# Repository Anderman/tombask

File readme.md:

Tosot (Gree) Hombask 200Liter

The signal is custom rs485

All message send
```
12-07 12:47:05 frame=7e 7e 00 f0 00 04 90 31 01 64 47 00 (poll slave 0x00)
12-07 12:47:06 frame=7e 7e 01 f0 00 04 90 31 01 74 87 00 (poll slave 0x01)
12-07 12:47:06 frame=7e 7e f0 01 02 2d 90 31 01 15 21 9a 40 4a 02 c0 02 05 01 c7 01 0c 02 0e 02 c4 00 24 01 17 b4 00 00 00 00 55 8e 5d a7 15 b0 8e 00 aa ff ff ff ff ff 73 4a 57 55 (response slave 0x01)
12-07 12:47:06 frame=7e 7e 02 f0 00 04 90 31 01 47 87 00 (poll slave 0x02)
12-07 12:47:06 frame=7e 7e f0 f0 04 2d 90 31 01 15 21 9a 40 4a 02 c0 02 05 01 c7 01 0c 02 0e 02 c4 00 24 01 17 b4 00 00 00 00 55 8e 5d a7 15 b0 8e 00 aa ff ff ff ff ff 73 73 f6 00 (broadcast master)
12-07 12:47:06 frame=7e 7e f0 f0 06 1c 90 31 01 15 2c c0 01 00 00 10 ff ff 00 00 af b4 04 4b 73 5f 5a 3a 4b 00 00 00 00 99 1f 00 (broadcast master)
12-07 12:47:07 frame=7e 7e f0 f0 02 3c 90 31 01 77 98 00 7d 00 00 00 00 76 00 74 75 00 00 10 01 01 90 00 00 00 00 f8 00 00 00 00 00 00 00 11 8c 0f 9f c6 1d 98 15 00 00 00 00 70 9a 00 00 00 00 02 00 00 00 00 02 00 00 5a f0 00 (broadcast master)
12-07 12:47:07 frame=7e 7e f0 f0 03 25 90 31 06 00 00 00 14 14 00 00 00 00 00 00 00 00 00 00 00 00 00 00 00 02 00 00 00 00 00 00 00 00 00 00 00 09 98 44 00 (broadcast master)
12-07 12:47:07 frame=7e 7e f0 f0 08 40 90 31 01 01 00 00 00 00 00 00 00 00 00 00 00 00 00 00 00 00 00 00 00 00 00 00 00 00 00 00 00 00 00 00 00 00 00 00 00 00 00 00 00 00 00 00 00 00 00 00 00 00 00 00 00 00 00 00 00 00 00 00 00 ae 60 00 (broadcast master)
```
Slave can send after a poll frame.
Slave is ready sending when the last padding byte is 0x55
To write byte 0x08 must be 0x02

Aansluiting Rs485 signal for wired controller on H1(pos) and H2(neg) of the XT3 connector

App 
## Control page

## temp history

## mtqq settings

## Logger (for debugging)

## wifi settings
This is the wifimanger plugin

PCB

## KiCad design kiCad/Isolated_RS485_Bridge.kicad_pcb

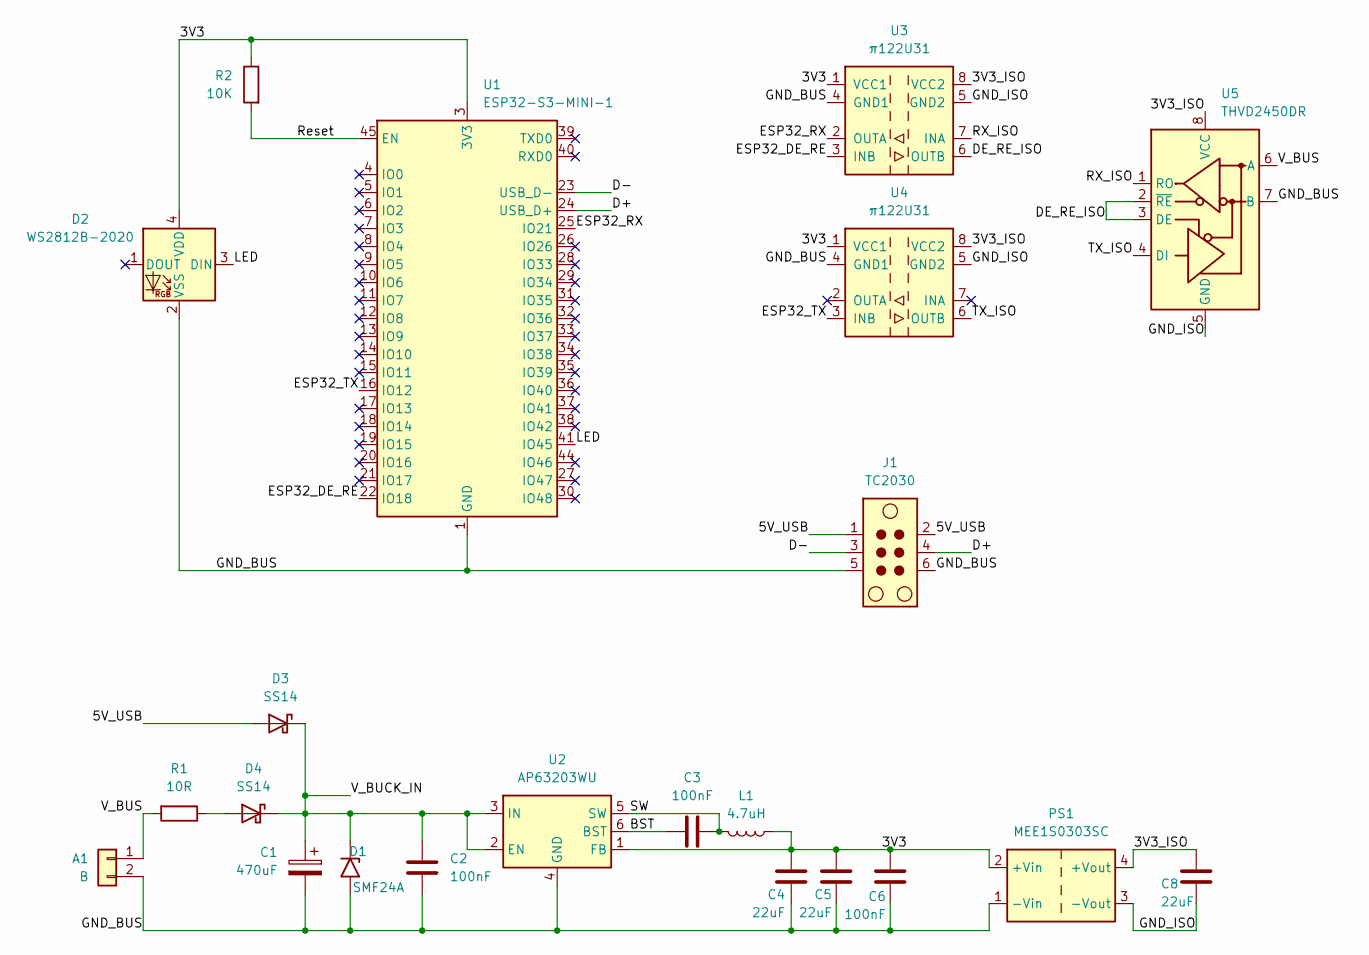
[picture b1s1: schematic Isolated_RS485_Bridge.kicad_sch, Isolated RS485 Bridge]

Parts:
A1: B; TerminalBlock_Phoenix_MKDS-1-2-3.81_1x02_P3.81mm_Horizontal; LCSC C5188452
C1: 470uF; CP_Elec_10x10; LCSC C3350
C2, C3, C6: 100nF; C_0603_1608Metric; LCSC C56476
C4, C5, C8: 22uF; C_0805_2012Metric; LCSC C45783
D1: SMF24A; D_SOD-123FL; LCSC C545276
D2: WS2812B-2020; LED_WS2812B-2020_2x2.2mm; LCSC C965555
D3, D4: SS14; D_SOD-323HE; LCSC C28646397
J1: TC2030; Tag-Connect_TC2030-IDC-NL_2x03_P1.27mm_Vertical
L1: 4.7uH; L_Bourns-SRN4018; LCSC C5159668
PS1: MEE1S0303SC; Converter_DCDC_Murata_MEE1SxxxxSC_THT; LCSC C7465185
R1: 10R; R_1206_3216Metric; LCSC C17903
R2: 10K; R_0603_1608Metric; LCSC C25804
U1: ESP32-S3-MINI-1; LCSC C3013941
U2: AP63203WU; TSOT-23-6; LCSC C780769
U3, U4: π122U31; SOIC-8_3.9x4.9mm_P1.27mm; LCSC C471590
U5: THVD2450DR; SOIC-8_3.9x4.9mm_P1.27mm; LCSC C2672621

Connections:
/3V3: C4.1, C5.1, C6.2, D2.4 (VDD), L1.1, PS1.2 (+Vin), R2.1, U1.3 (3V3), U2.1 (FB), U3.1 (VCC1), U4.1 (VCC1)
/3V3_ISO: C8.1, PS1.4 (+Vout), U3.8 (VCC2), U4.8 (VCC2), U5.8 (VCC)
/5V_USB: D3.2 (A), J1.1, J1.2
/BST: C3.2, U2.6 (BST)
/D+: J1.4, U1.24 (USB_D+)
/D-: J1.3, U1.23 (USB_D-)
/DE_RE_ISO: U3.6 (OUTB), U5.2 (~RE), U5.3 (DE)
/ESP32_DE_RE: U1.22 (IO18), U3.3 (INB)
/ESP32_RX: U1.25 (IO21), U3.2 (OUTA)
/ESP32_TX: U1.16 (IO12), U4.3 (INB)
/GND_BUS: A1.2, C1.2, C2.2, C4.2, C5.2, C6.1, D1.2 (A2), D2.2 (VSS), J1.5, J1.6, PS1.1 (-Vin), U1.1 (GND), U1.2 (GND), U1.42 (GND), U1.43 (GND), U1.46 (GND), U1.47 (GND), U1.48 (GND), U1.49 (GND), U1.50 (GND), U1.51 (GND), U1.52 (GND), U1.53 (GND), U1.54 (GND), U1.55 (GND), U1.56 (GND), U1.57 (GND), U1.58 (GND), U1.59 (GND), U1.60 (GND), U1.61 (GND), U1.62 (GND), U1.63 (GND), U1.64 (GND), U1.65 (GND), U2.4 (GND), U3.4 (GND1), U4.4 (GND1), U5.7 (B)
/GND_ISO: C8.2, PS1.3 (-Vout), U3.5 (GND2), U4.5 (GND2), U5.5 (GND)
/LED: D2.3 (DIN), U1.41 (IO45)
/RX_ISO: U3.7 (INA), U5.1 (RO)
/Reset: R2.2, U1.45 (EN)
/SW: C3.1, L1.2, U2.5 (SW)
/TX_ISO: U4.6 (OUTB), U5.4 (DI)
/V_BUCK_IN: C1.1, C2.1, D1.1 (A1), D3.1 (K), D4.1 (K), U2.2 (EN), U2.3 (IN)
/V_BUS: A1.1, R1.2, U5.6 (A)
unnamed: D4.2 (A), R1.1

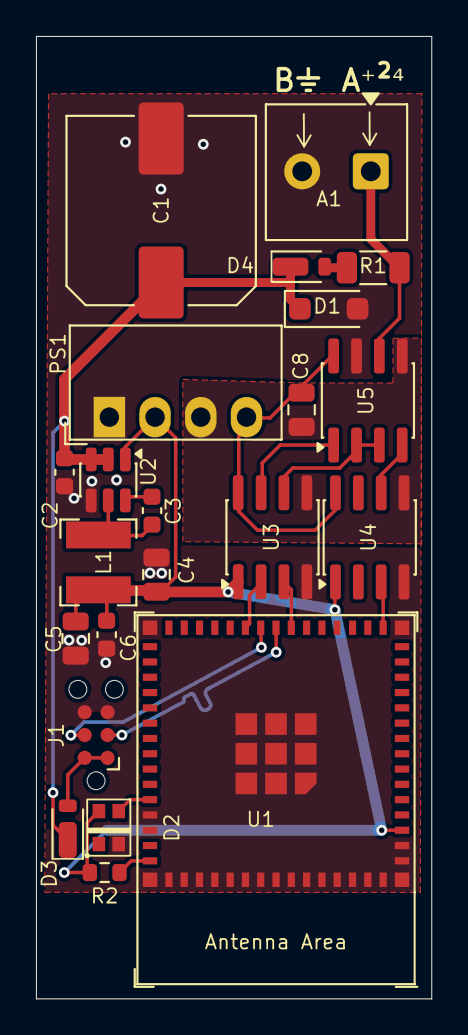
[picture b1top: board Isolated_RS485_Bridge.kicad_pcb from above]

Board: 2 copper layers, 22.0 x 53.5 mm, 22 parts (0 on the bottom side), 20 nets.

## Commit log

2025-12-07 init
2025-12-26 refactor
2025-12-28 Add new webui
2025-12-31 UPdate UI
2025-12-31 add kicad
2026-01-05 Add Pcb
2026-03-30 first working version with last kicad design
2026-03-30 check auto update
2026-03-30 test auto update
